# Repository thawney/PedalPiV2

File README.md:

# PedalPi
Pedal Pi Thawney is based off of Pedal-Pi by electrosmash; a lo-fi programmable guitar pedal that works with the Raspberry Pi ZERO Board. 

## How Is this Repository different to the original Pedal Pi?

The difference is that my version also has open source PCB files, Protective Case Design files, and anything else needed to make the project work (as well as example code of various pugins), unlike electrosmash who claims to be open source but will not share or does not produce certain files (such as PCB files and Protective case designs)

# How Does the Circuit Work?

This  [_hat_](https://www.hifiberry.com/blog/what-is-a-raspberry-pi-hat/) has three parts:

-   The Input Stage:  Amplifies and filters the guitar signal making it ready for the ADC (Analog to Digital Converter). The ADC sends the signal to the PI ZERO using  [SPI communication](https://en.wikipedia.org/wiki/Serial_Peripheral_Interface_Bus). In the forum, the topic "[Using MCP3202 ADC with Raspberry Pi Zero](https://www.electrosmash.com/forum/pedal-pi/212-using-mcp3202-adc-with-raspberry-pi-zero)" gives more details about the ADC-Pi ZERO connection.  
    
-   Pi ZERO:  It takes the digitalized audio waveform from the ADC and does all the Digital Signal Processing (DSP) creating effects (distortion, fuzz, delay, echo, tremolo...). In the forum, the topic "[Basics of Audio DSP in C for Raspberry Pi Zero](https://www.electrosmash.com/forum/pedal-pi/207-basics-of-audio-dsp-in-c-for-rapsberry-pi-zero)" can assist you to learn the basics.
-   The Output Stage:  Once the new digital waveform is created, the Pi Zero creates an analog signal with two PWMs combined, the signal is filtered and prepared to be sent to the next pedal or the guitar amp.  For more info check the topic "[PWM Audio on Raspberry Pi Zero](https://www.electrosmash.com/forum/pedal-pi/210-pwm-audio-on-raspberry-pi-zero)".

- Here is a more detailed photo of just the RaspberryPi Stage.

# How to Program it?

The idea is to make it as easy as possible, the examples are programmed in C using the standard  [BCM2835 Libraries](http://www.airspayce.com/mikem/bcm2835/). The Operating System used is  [Raspbian.](https://www.raspberrypi.org/downloads/raspbian/)  All tools and programs are free/open source. In the OFFICIAL forum, there is a topic called  ["How to Start Programming Pedal-Pi"](https://www.electrosmash.com/forum/pedal-pi/202-how-to-start-programming-pedal-pi) with more details (note: this forum is not run or maintained by thawney and is for the original design, all code should still work).

Basic knowledge of Arduino, Linux and C are needed. You can find many Example effects in this repository's Effects folder, the PedalPi legacy effect are the most basic ones currently.

## Need More Support?

Contact Thawney:

- Find all of their social media and othe contact info [here](https://www.thawney.com) or join their [discord](https://discord.com/invite/Eh7VRgu).

ElectroSmash PedalPi Website:

- Whilst some may be very outdated, information on how the project works, old schematics and Learning materials can be found [here](https://www.electrosmash.com/pedal-pi).

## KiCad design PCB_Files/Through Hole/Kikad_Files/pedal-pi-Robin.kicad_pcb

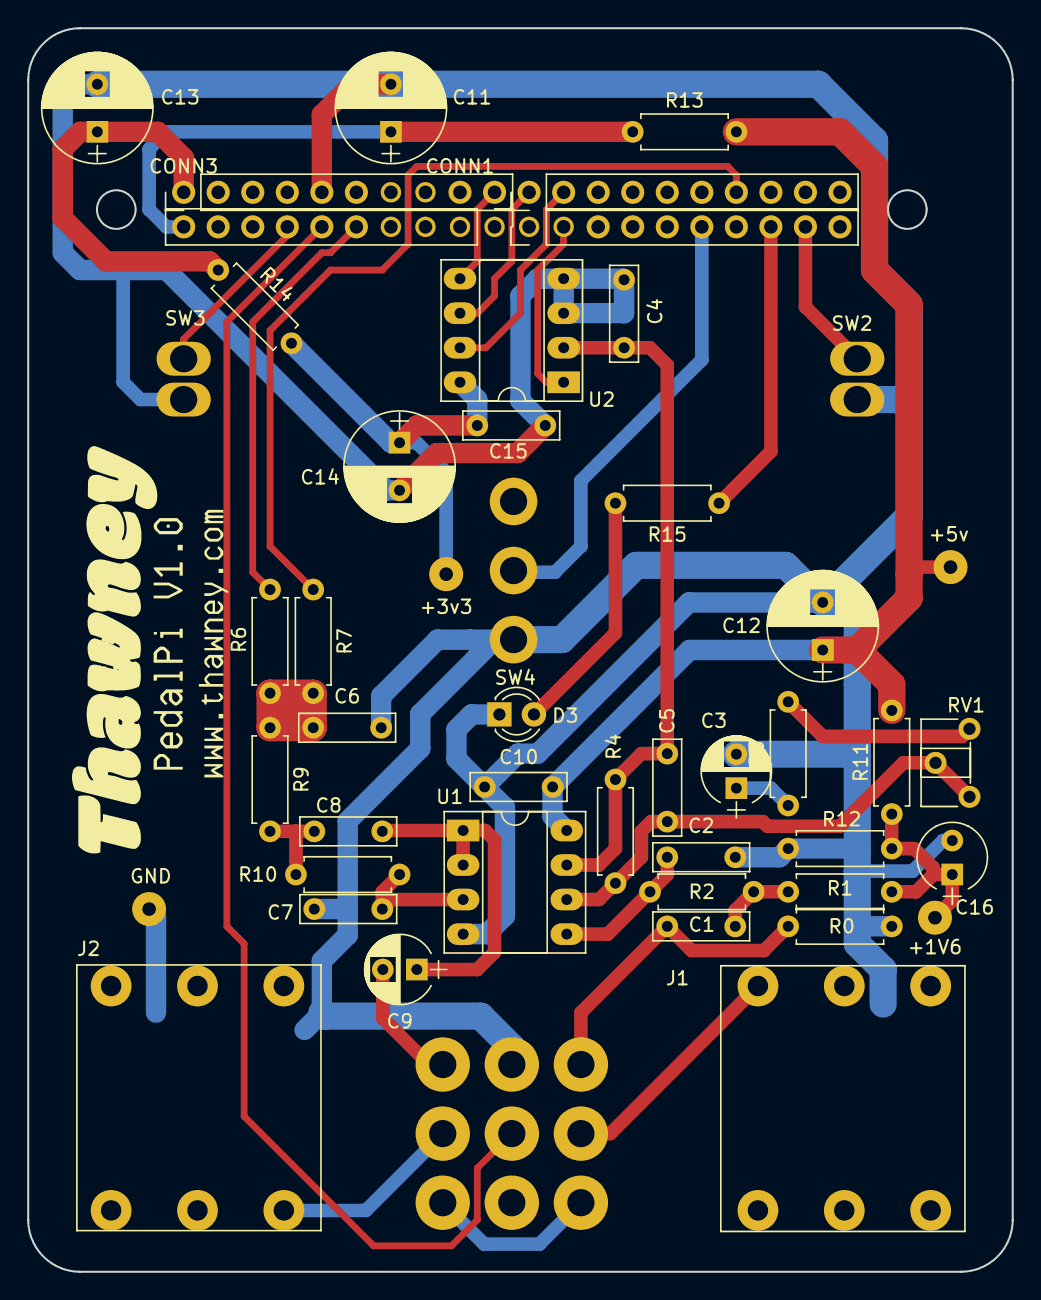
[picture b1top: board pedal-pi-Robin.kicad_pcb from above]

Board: 2 copper layers, 72.4 x 91.4 mm, 48 parts (1 on the bottom side), 33 nets.

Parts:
+1V6: 1V6 TP; SolderWirePad_single_1mmDrill
+3v3: 3V3 TP; SolderWirePad_single_1mmDrill
+5v: 5V TP; SolderWirePad_single_1mmDrill
C1: 0.1u; C_Rect_L7.0mm_W2.0mm_P5.00mm
C2, C4, C6, C7, C8: 6n8; C_Rect_L7.0mm_W2.0mm_P5.00mm
C3, C9: 4.7u; CP_Radial_D5.0mm_P2.50mm
C5: 270p; C_Rect_L7.0mm_W2.0mm_P5.00mm
C10, C15: 100n; C_Rect_L7.0mm_W2.0mm_P5.00mm
C11, C12, C13, C14: 220u; CP_Radial_D8.0mm_P3.50mm
C16: 4.7u; CP_Radial_Tantal_D5.0mm_P2.50mm
CONN1, CONN2, CONN3, CONN4: CONN_10pins; Pin_Header_Straight_1x10_Pitch2.54mm
D3: LED; LED_D3.0mm
GND: GND TP; SolderWirePad_single_1mmDrill
J1: Guitar_IN; StereoJack-NYS216_2
J2: OUTPUT; StereoJack-NYS216_2
R0, R1: 1M; R_Axial_DIN0207_L6.3mm_D2.5mm_P7.62mm_Horizontal
R2, R6, R9, R10, R13, R14: 4K7; R_Axial_DIN0207_L6.3mm_D2.5mm_P7.62mm_Horizontal
R3, R15: 4.7K; R_Axial_DIN0207_L6.3mm_D2.5mm_P7.62mm_Horizontal
R4, R11: 100K; R_Axial_DIN0207_L6.3mm_D2.5mm_P7.62mm_Horizontal
R7: 300K; R_Axial_DIN0207_L6.3mm_D2.5mm_P7.62mm_Horizontal
R12: 50K; R_Axial_DIN0207_L6.3mm_D2.5mm_P7.62mm_Horizontal
RV1: 500K; Potentiometer_Trimmer_ACP_CA6h_Vertical
SW1: SWITCH_3PDT; 3PDTswitch
SW2, SW3: SW_PUSH; Switch2
SW4: SWITCH_INV; Switch
U1: MCP6002; DIP-8_W7.62mm_Socket_LongPads
U2: MCP3002; DIP-8_W7.62mm_Socket_LongPads

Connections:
+1V5: +1V6.1, C16.1, R1.2, R11.2, R12.1
+3.3VADC: +3v3.1, C14.1, C15.1, R14.2, U2.8
+3V3: C13.1, CONN3.1, R14.1
+5V: C11.1, CONN1.10, R13.1
+5VA: +5v.1, C10.1, C12.1, R11.1, R13.2, U1.8
/ADC0: C4.1, C5.1, R4.2, U1.7, U2.2
/Bypass: SW1.3, SW1.9
/FX In: C1.1, R0.1, SW1.7
/FX Out: C9.2, SW1.1
/GPIO12: CONN2.6, SW4.2
/GPIO14: CONN1.7, SW3.1
/GPIO15: CONN1.6, SW1.5
/GPIO16: CONN2.8, R15.1
/GPIO20: CONN2.9, SW2.1
/Input Jack: J1.1, SW1.8
/Output JAck: J2.1, SW1.2
/PWM0: CONN1.5, R6.1
/PWM1: CONN4.7, R7.1
/SPI_CLK: CONN4.2, U2.7
/SPI_CS: CONN2.2, U2.1
/SPI_MISO: CONN4.1, U2.6
/SPI_MOSI: CONN3.10, U2.5
GND: C2.2, C3.2, C4.2, C6.2, C7.2, C10.2, C11.2, C12.2, C13.2, C14.2, C15.2, C16.2, CONN3.5, D3.1, GND.1, J1.2, J1.3, J2.2, J2.3, R0.2, R12.2, SW1.4, SW2.2, SW3.2, SW4.3, U1.4, U2.3, U2.4
unnamed: C1.2, R1.1, R2.1
unnamed: C2.1, R2.2, U1.5
unnamed: C3.1, R3.1
unnamed: C5.2, R4.1, RV1.1, RV1.2, U1.6
unnamed: C6.1, R6.2, R7.2, R9.1
unnamed: C7.1, R10.2, U1.3
unnamed: C8.1, C9.1, U1.1, U1.2
unnamed: C8.2, R9.2, R10.1
unnamed: D3.2, R15.2
unnamed: R3.2, RV1.3

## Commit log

2022-07-13 Create README.md
    Created initial readme
2022-07-13 Organised Project
    moved effect files to an effects folder. Legacy plugins are old electrosmash effects
2022-07-13 Added V1 PCB Files
    Includes images of the pcb design, Kikad files to edit your own version and premade gerber files to produce your own pcb
2022-07-14 Create Electronics_Components_List.csv
    Components needed for V1.0 Some Components may be different to the original ElectroSmash list as their components list contains discontinued parts.
2022-07-14 added info to readme :D3
2022-07-14 Update README.md
    fixed broken image
2022-07-15 Added Folder For Cases
    Added case folder and also made explanation Doc
2022-07-15 Set theme jekyll-theme-cayman
2022-07-15 moved readme
2022-07-15 moved cases
2022-07-15 Update index.md
    made same as readme
2022-07-15 merged index page and readme
2022-07-15 fixed broken links
2022-07-23 added stuff for SMD pcb
2022-08-14 Updated Components List
2022-09-13 cropped images and edited smd
2022-10-25 added image of wip PCB
2022-12-01 Added The First Case - Laser Cuttable
    It is a basic case for the pedal pi to be cut on 3mm Material. F3d file on fusion 360 to edit source or dxf for maximum compatibility.
2022-12-09 added video link
2022-12-09 Added Final Demo Image
2022-12-09 Added Functional Image
2023-01-18 new images
    added image of complete pedalpi!
2023-01-21 new images
